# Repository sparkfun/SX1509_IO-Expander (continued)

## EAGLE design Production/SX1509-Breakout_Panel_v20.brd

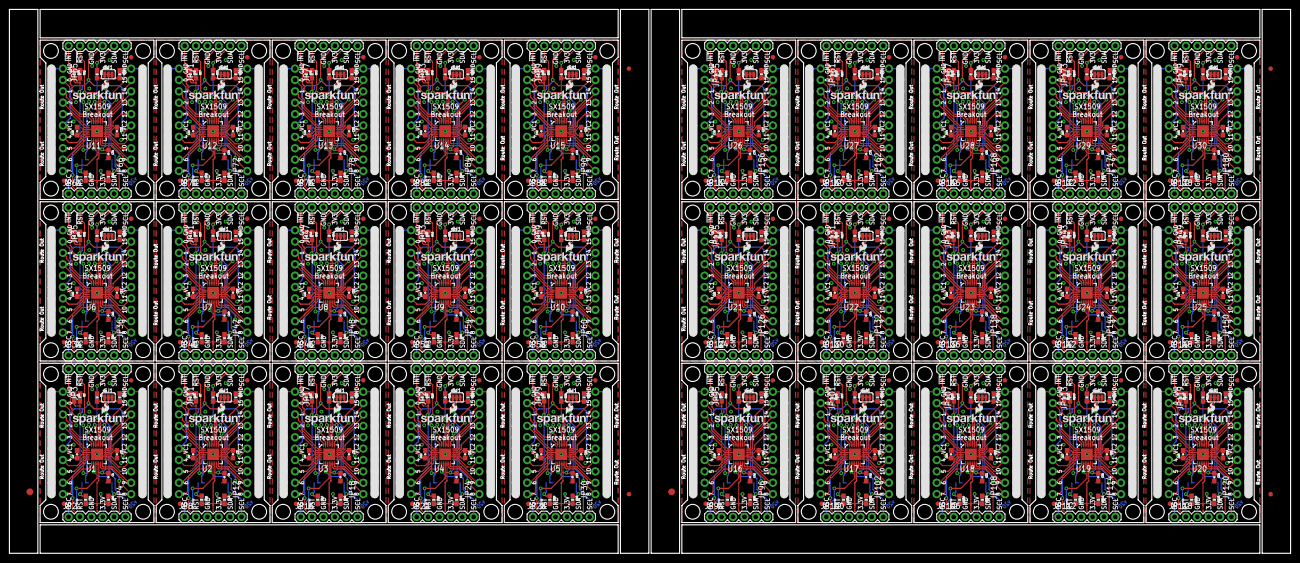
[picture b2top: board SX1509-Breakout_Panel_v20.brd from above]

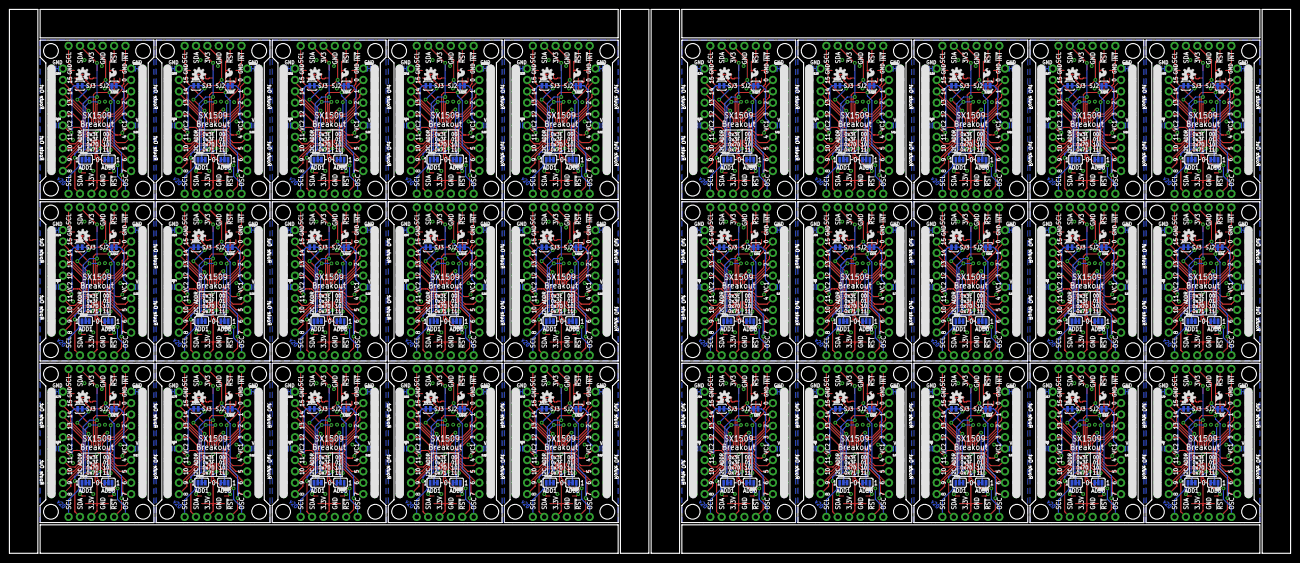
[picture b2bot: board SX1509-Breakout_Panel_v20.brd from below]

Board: 2 copper layers, 286.0 x 121.4 mm, 966 parts (300 on the bottom side), 990 nets.

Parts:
C1, C2, C3, C4, C5, C6, C7, C8, C9, C10, C11, C12, C13, C14, C15, C16, C17, C18, C19, C20, C21, C22, C23, C24, C25, C26, C27, C28, C29, C30, C31, C32, C33, C34, C35, C36, C37, C38, C39, C40, C41, C42, C43, C44, C45, C46, C47, C48, C49, C50, C51, C52, C53, C54, C55, C56, C57, C58, C59, C60, C61, C62, C63, C64, C65, C66, C67, C68, C69, C70, C71, C72, C73, C74, C75, C76, C77, C78, C79, C80, C81, C82, C83, C84, C85, C86, C87, C88, C89, C90: 0.1uF; 0603-CAP
E$1, E$6: FIDUCIAL-1.5X3
E$2, E$3, E$4, E$5: FIDUCIAL-1X2
JP1, JP2, JP7, JP8, JP15, JP16, JP21, JP22, JP27, JP28, JP33, JP34, JP39, JP40, JP45, JP46, JP51, JP52, JP57, JP58, JP63, JP64, JP69, JP70, JP75, JP76, JP81, JP82, JP87, JP88, JP93, JP94, JP99, JP100, JP105, JP106, JP111, JP112, JP117, JP118, JP123, JP124, JP129, JP130, JP135, JP136, JP141, JP142, JP147, JP148, JP153, JP154, JP159, JP160, JP165, JP166, JP171, JP172, JP177, JP178: 1X06
JP3, JP4, JP11, JP12, JP17, JP18, JP23, JP24, JP29, JP30, JP35, JP36, JP41, JP42, JP47, JP48, JP53, JP54, JP59, JP60, JP65, JP66, JP71, JP72, JP77, JP78, JP83, JP84, JP89, JP90, JP95, JP96, JP101, JP102, JP107, JP108, JP113, JP114, JP119, JP120, JP125, JP126, JP131, JP132, JP137, JP138, JP143, JP144, JP149, JP150, JP155, JP156, JP161, JP162, JP167, JP168, JP173, JP174, JP179, JP180: 2X10_ROUND_NOSILK
JP5, JP6, JP9, JP10, JP13, JP14, JP19, JP20, JP25, JP26, JP31, JP32, JP37, JP38, JP43, JP44, JP49, JP50, JP55, JP56, JP61, JP62, JP67, JP68, JP73, JP74, JP79, JP80, JP85, JP86, JP91, JP92, JP97, JP98, JP103, JP104, JP109, JP110, JP115, JP116, JP121, JP122, JP127, JP128, JP133, JP134, JP139, JP140, JP145, JP146, JP151, JP152, JP157, JP158, JP163, JP164, JP169, JP170, JP175, JP176: FIDUCIAL1X2; FIDUCIAL-1X2
LOGO1, LOGO6, LOGO9, LOGO12, LOGO15, LOGO18, LOGO21, LOGO24, LOGO27, LOGO30, LOGO33, LOGO36, LOGO39, LOGO42, LOGO45, LOGO48, LOGO51, LOGO54, LOGO57, LOGO60, LOGO63, LOGO66, LOGO69, LOGO72, LOGO75, LOGO78, LOGO81, LOGO84, LOGO87, LOGO90: SFE_LOGO_NAME_FLAME.1_INCH; SFE_LOGO_NAME_FLAME_.1
LOGO2, LOGO5, LOGO8, LOGO11, LOGO14, LOGO17, LOGO20, LOGO23, LOGO26, LOGO29, LOGO32, LOGO35, LOGO38, LOGO41, LOGO44, LOGO47, LOGO50, LOGO53, LOGO56, LOGO59, LOGO62, LOGO65, LOGO68, LOGO71, LOGO74, LOGO77, LOGO80, LOGO83, LOGO86, LOGO89: SFE_LOGO_FLAME.1_INCH; SFE_LOGO_FLAME_.1
LOGO3, LOGO4, LOGO7, LOGO10, LOGO13, LOGO16, LOGO19, LOGO22, LOGO25, LOGO28, LOGO31, LOGO34, LOGO37, LOGO40, LOGO43, LOGO46, LOGO49, LOGO52, LOGO55, LOGO58, LOGO61, LOGO64, LOGO67, LOGO70, LOGO73, LOGO76, LOGO79, LOGO82, LOGO85, LOGO88: OSHW-LOGOS; OSHW-LOGO-S
R1, R2, R3, R4, R5, R6, R7, R8, R9, R10, R11, R12, R13, R14, R15, R16, R17, R18, R19, R20, R21, R22, R23, R24, R25, R26, R27, R28, R29, R30, R31, R32, R33, R34, R35, R36, R37, R38, R39, R40, R41, R42, R43, R44, R45, R46, R47, R48, R49, R50, R51, R52, R53, R54, R55, R56, R57, R58, R59, R60, R61, R62, R63, R64, R65, R66, R67, R68, R69, R70, R71, R72, R73, R74, R75, R76, R77, R78, R79, R80, R81, R82, R83, R84, R85, R86, R87, R88, R89, R90, R91, R92, R93, R94, R95, R96, R97, R98, R99, R100, R101, R102, R103, R104, R105, R106, R107, R108, R109, R110, R111, R112, R113, R114, R115, R116, R117, R118, R119, R120, R121, R122, R123, R124, R125, R126, R127, R128, R129, R130, R131, R132, R133, R134, R135, R136, R137, R138, R139, R140, R141, R142, R143, R144, R145, R146, R147, R148, R149, R150, R151, R152, R153, R154, R155, R156, R157, R158, R159, R160, R161, R162, R163, R164, R165, R166, R167, R168, R169, R170, R171, R172, R173, R174, R175, R176, R177, R178, R179, R180: 10K; 0603-RES
SJ1, SJ14, SJ23, SJ32, SJ41, SJ50, SJ59, SJ68, SJ77, SJ86, SJ95, SJ104, SJ113, SJ122, SJ131, SJ140, SJ149, SJ158, SJ167, SJ176, SJ185, SJ194, SJ203, SJ212, SJ221, SJ230, SJ239, SJ248, SJ257, SJ266: PAD-JUMPER-3-3OF3_NC_BY_TRACE_YES_SILK_FULL_BOX
SJ2, SJ10, SJ19, SJ28, SJ37, SJ46, SJ55, SJ64, SJ73, SJ82, SJ91, SJ100, SJ109, SJ118, SJ127, SJ136, SJ145, SJ154, SJ163, SJ172, SJ181, SJ190, SJ199, SJ208, SJ217, SJ226, SJ235, SJ244, SJ253, SJ262: VCC1-3.3V; PAD-JUMPER-2-NC_BY_TRACE_YES_SILK
SJ3, SJ11, SJ20, SJ29, SJ38, SJ47, SJ56, SJ65, SJ74, SJ83, SJ92, SJ101, SJ110, SJ119, SJ128, SJ137, SJ146, SJ155, SJ164, SJ173, SJ182, SJ191, SJ200, SJ209, SJ218, SJ227, SJ236, SJ245, SJ254, SJ263: VCC2-3.3V; PAD-JUMPER-2-NC_BY_TRACE_YES_SILK
SJ4, SJ5, SJ12, SJ13, SJ21, SJ22, SJ30, SJ31, SJ39, SJ40, SJ48, SJ49, SJ57, SJ58, SJ66, SJ67, SJ75, SJ76, SJ84, SJ85, SJ93, SJ94, SJ102, SJ103, SJ111, SJ112, SJ120, SJ121, SJ129, SJ130, SJ138, SJ139, SJ147, SJ148, SJ156, SJ157, SJ165, SJ166, SJ174, SJ175, SJ183, SJ184, SJ192, SJ193, SJ201, SJ202, SJ210, SJ211, SJ219, SJ220, SJ228, SJ229, SJ237, SJ238, SJ246, SJ247, SJ255, SJ256, SJ264, SJ265: PAD-JUMPER-3-2OF3_NC_BY_TRACE_YES_SILK_FULL_BOX
SJ6, SJ15, SJ24, SJ33, SJ42, SJ51, SJ60, SJ69, SJ78, SJ87, SJ96, SJ105, SJ114, SJ123, SJ132, SJ141, SJ150, SJ159, SJ168, SJ177, SJ186, SJ195, SJ204, SJ213, SJ222, SJ231, SJ240, SJ249, SJ258, SJ267: A-VCC1; PAD-JUMPER-2-NO_NO_SILK
SJ7, SJ9, SJ17, SJ18, SJ26, SJ27, SJ35, SJ36, SJ44, SJ45, SJ53, SJ54, SJ62, SJ63, SJ71, SJ72, SJ80, SJ81, SJ89, SJ90, SJ98, SJ99, SJ107, SJ108, SJ116, SJ117, SJ125, SJ126, SJ134, SJ135, SJ143, SJ144, SJ152, SJ153, SJ161, SJ162, SJ170, SJ171, SJ179, SJ180, SJ188, SJ189, SJ197, SJ198, SJ206, SJ207, SJ215, SJ216, SJ224, SJ225, SJ233, SJ234, SJ242, SJ243, SJ251, SJ252, SJ260, SJ261, SJ269, SJ270: GND; PAD-JUMPER-2-NC_BY_TRACE_NO_SILK
SJ8, SJ16, SJ25, SJ34, SJ43, SJ52, SJ61, SJ70, SJ79, SJ88, SJ97, SJ106, SJ115, SJ124, SJ133, SJ142, SJ151, SJ160, SJ169, SJ178, SJ187, SJ196, SJ205, SJ214, SJ223, SJ232, SJ241, SJ250, SJ259, SJ268: B-VCC2; PAD-JUMPER-2-NO_NO_SILK
STANDOFF1, STANDOFF2, STANDOFF3, STANDOFF4, STANDOFF5, STANDOFF6, STANDOFF7, STANDOFF8, STANDOFF9, STANDOFF10, STANDOFF11, STANDOFF12, STANDOFF13, STANDOFF14, STANDOFF15, STANDOFF16, STANDOFF17, STANDOFF18, STANDOFF19, STANDOFF20, STANDOFF21, STANDOFF22, STANDOFF23, STANDOFF24, STANDOFF25, STANDOFF26, STANDOFF27, STANDOFF28, STANDOFF29, STANDOFF30, STANDOFF31, STANDOFF32, STANDOFF33, STANDOFF34, STANDOFF35, STANDOFF36, STANDOFF37, STANDOFF38, STANDOFF39, STANDOFF40, STANDOFF41, STANDOFF42, STANDOFF43, STANDOFF44, STANDOFF45, STANDOFF46, STANDOFF47, STANDOFF48, STANDOFF49, STANDOFF50, STANDOFF51, STANDOFF52, STANDOFF53, STANDOFF54, STANDOFF55, STANDOFF56, STANDOFF57, STANDOFF58, STANDOFF59, STANDOFF60, STANDOFF61, STANDOFF62, STANDOFF63, STANDOFF64, STANDOFF65, STANDOFF66, STANDOFF67, STANDOFF68, STANDOFF69, STANDOFF70, STANDOFF71, STANDOFF72, STANDOFF73, STANDOFF74, STANDOFF75, STANDOFF76, STANDOFF77, STANDOFF78, STANDOFF79, STANDOFF80, STANDOFF81, STANDOFF82, STANDOFF83, STANDOFF84, STANDOFF85, STANDOFF86, STANDOFF87, STANDOFF88, STANDOFF89, STANDOFF90, STANDOFF91, STANDOFF92, STANDOFF93, STANDOFF94, STANDOFF95, STANDOFF96, STANDOFF97, STANDOFF98, STANDOFF99, STANDOFF100, STANDOFF101, STANDOFF102, STANDOFF103, STANDOFF104, STANDOFF105, STANDOFF106, STANDOFF107, STANDOFF108, STANDOFF109, STANDOFF110, STANDOFF111, STANDOFF112, STANDOFF113, STANDOFF114, STANDOFF115, STANDOFF116, STANDOFF117, STANDOFF118, STANDOFF119, STANDOFF120: STAND-OFF
U1, U2, U3, U4, U5, U6, U7, U8, U9, U10, U11, U12, U13, U14, U15, U16, U17, U18, U19, U20, U21, U22, U23, U24, U25, U26, U27, U28, U29, U30: SX1509; QFN-28

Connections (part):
0: JP3.4, U1.27
1: JP3.6, U1.28
2: JP3.8, U1.1
3: JP3.10, U1.2
3.3V: C1.1, JP1.4, JP2.4, R1.2, R3.2, R5.2, R6.2, SJ1.2, SJ2.2, SJ3.2, U1.12
3.3V1: C4.1, JP7.4, JP8.4, R7.2, R10.2, R11.2, R12.2, SJ10.2, SJ11.2, SJ14.2, U2.12
3.3V2: C7.1, JP15.4, JP16.4, R13.2, R16.2, R17.2, R18.2, SJ19.2, SJ20.2, SJ23.2, U3.12
3.3V3: C10.1, JP21.4, JP22.4, R19.2, R22.2, R23.2, R24.2, SJ28.2, SJ29.2, SJ32.2, U4.12
3.3V4: C13.1, JP27.4, JP28.4, R25.2, R28.2, R29.2, R30.2, SJ37.2, SJ38.2, SJ41.2, U5.12
3.3V5: C16.1, JP33.4, JP34.4, R31.2, R34.2, R35.2, R36.2, SJ46.2, SJ47.2, SJ50.2, U6.12
3.3V6: C19.1, JP39.4, JP40.4, R37.2, R40.2, R41.2, R42.2, SJ55.2, SJ56.2, SJ59.2, U7.12
3.3V7: C22.1, JP45.4, JP46.4, R43.2, R46.2, R47.2, R48.2, SJ64.2, SJ65.2, SJ68.2, U8.12
3.3V8: C25.1, JP51.4, JP52.4, R49.2, R52.2, R53.2, R54.2, SJ73.2, SJ74.2, SJ77.2, U9.12
3.3V9: C28.1, JP57.4, JP58.4, R55.2, R58.2, R59.2, R60.2, SJ82.2, SJ83.2, SJ86.2, U10.12
3.3V10: C31.1, JP63.4, JP64.4, R61.2, R64.2, R65.2, R66.2, SJ91.2, SJ92.2, SJ95.2, U11.12
3.3V11: C34.1, JP69.4, JP70.4, R67.2, R70.2, R71.2, R72.2, SJ100.2, SJ101.2, SJ104.2, U12.12
3.3V12: C37.1, JP75.4, JP76.4, R73.2, R76.2, R77.2, R78.2, SJ109.2, SJ110.2, SJ113.2, U13.12
3.3V13: C40.1, JP81.4, JP82.4, R79.2, R82.2, R83.2, R84.2, SJ118.2, SJ119.2, SJ122.2, U14.12
3.3V14: C43.1, JP87.4, JP88.4, R85.2, R88.2, R89.2, R90.2, SJ127.2, SJ128.2, SJ131.2, U15.12
3.3V15: C46.1, JP93.4, JP94.4, R91.2, R94.2, R95.2, R96.2, SJ136.2, SJ137.2, SJ140.2, U16.12
3.3V16: C49.1, JP99.4, JP100.4, R97.2, R100.2, R101.2, R102.2, SJ145.2, SJ146.2, SJ149.2, U17.12
3.3V17: C52.1, JP105.4, JP106.4, R103.2, R106.2, R107.2, R108.2, SJ154.2, SJ155.2, SJ158.2, U18.12
3.3V18: C55.1, JP111.4, JP112.4, R109.2, R112.2, R113.2, R114.2, SJ163.2, SJ164.2, SJ167.2, U19.12
3.3V19: C58.1, JP117.4, JP118.4, R115.2, R118.2, R119.2, R120.2, SJ172.2, SJ173.2, SJ176.2, U20.12
3.3V20: C61.1, JP123.4, JP124.4, R121.2, R124.2, R125.2, R126.2, SJ181.2, SJ182.2, SJ185.2, U21.12
3.3V21: C64.1, JP129.4, JP130.4, R127.2, R130.2, R131.2, R132.2, SJ190.2, SJ191.2, SJ194.2, U22.12
3.3V22: C67.1, JP135.4, JP136.4, R133.2, R136.2, R137.2, R138.2, SJ199.2, SJ200.2, SJ203.2, U23.12
3.3V23: C70.1, JP141.4, JP142.4, R139.2, R142.2, R143.2, R144.2, SJ208.2, SJ209.2, SJ212.2, U24.12
3.3V24: C73.1, JP147.4, JP148.4, R145.2, R148.2, R149.2, R150.2, SJ217.2, SJ218.2, SJ221.2, U25.12
3.3V25: C76.1, JP153.4, JP154.4, R151.2, R154.2, R155.2, R156.2, SJ226.2, SJ227.2, SJ230.2, U26.12
3.3V26: C79.1, JP159.4, JP160.4, R157.2, R160.2, R161.2, R162.2, SJ235.2, SJ236.2, SJ239.2, U27.12
3.3V27: C82.1, JP165.4, JP166.4, R163.2, R166.2, R167.2, R168.2, SJ244.2, SJ245.2, SJ248.2, U28.12
3.3V28: C85.1, JP171.4, JP172.4, R169.2, R172.2, R173.2, R174.2, SJ253.2, SJ254.2, SJ257.2, U29.12
3.3V29: C88.1, JP177.4, JP178.4, R175.2, R178.2, R179.2, R180.2, SJ262.2, SJ263.2, SJ266.2, U30.12
4: JP3.14, U1.5
5: JP3.16, U1.6
6: JP3.18, U1.7
7: JP3.20, U1.8
8: JP4.2, U1.13
9: JP4.4, U1.14
10: JP4.6, U1.15
11: JP4.8, U1.16
12: JP4.12, U1.19
13: JP4.14, U1.20
14: JP4.16, U1.21
15: JP4.18, U1.22
16: JP12.2, U2.13
17: JP12.4, U2.14
18: JP12.6, U2.15
19: JP12.8, U2.16
20: JP12.12, U2.19
21: JP12.14, U2.20
22: JP12.16, U2.21
23: JP12.18, U2.22
24: JP11.4, U2.27
25: JP11.6, U2.28
26: JP11.8, U2.1
27: JP11.10, U2.2
28: JP11.14, U2.5
29: JP11.16, U2.6
30: JP11.18, U2.7
31: JP11.20, U2.8
32: JP18.2, U3.13
33: JP18.4, U3.14
34: JP18.6, U3.15
35: JP18.8, U3.16
36: JP18.12, U3.19
37: JP18.14, U3.20
38: JP18.16, U3.21
39: JP18.18, U3.22
40: JP17.4, U3.27
41: JP17.6, U3.28
42: JP17.8, U3.1
43: JP17.10, U3.2
44: JP17.14, U3.5
45: JP17.16, U3.6
46: JP17.18, U3.7
47: JP17.20, U3.8
48: JP24.2, U4.13
49: JP24.4, U4.14
50: JP24.6, U4.15
51: JP24.8, U4.16
52: JP24.12, U4.19
53: JP24.14, U4.20
54: JP24.16, U4.21
55: JP24.18, U4.22
56: JP23.4, U4.27
57: JP23.6, U4.28
58: JP23.8, U4.1
59: JP23.10, U4.2
60: JP23.14, U4.5
61: JP23.16, U4.6
62: JP23.18, U4.7
63: JP23.20, U4.8
64: JP30.2, U5.13
65: JP30.4, U5.14
66: JP30.6, U5.15
67: JP30.8, U5.16
68: JP30.12, U5.19
69: JP30.14, U5.20
70: JP30.16, U5.21
71: JP30.18, U5.22
72: JP29.4, U5.27
73: JP29.6, U5.28
74: JP29.8, U5.1
75: JP29.10, U5.2
76: JP29.14, U5.5
77: JP29.16, U5.6
78: JP29.18, U5.7
79: JP29.20, U5.8
80: JP36.2, U6.13
81: JP36.4, U6.14
82: JP36.6, U6.15
83: JP36.8, U6.16
84: JP36.12, U6.19
85: JP36.14, U6.20
86: JP36.16, U6.21
87: JP36.18, U6.22
88: JP35.4, U6.27
89: JP35.6, U6.28
90: JP35.8, U6.1
91: JP35.10, U6.2
92: JP35.14, U6.5
93: JP35.16, U6.6
94: JP35.18, U6.7
95: JP35.20, U6.8
96: JP42.2, U7.13
97: JP42.4, U7.14
98: JP42.6, U7.15
99: JP42.8, U7.16
100: JP42.12, U7.19
101: JP42.14, U7.20
102: JP42.16, U7.21
103: JP42.18, U7.22
104: JP41.4, U7.27
105: JP41.6, U7.28
106: JP41.8, U7.1
107: JP41.10, U7.2
108: JP41.14, U7.5
109: JP41.16, U7.6
110: JP41.18, U7.7
111: JP41.20, U7.8
112: JP48.2, U8.13
113: JP48.4, U8.14
114: JP48.6, U8.15
115: JP48.8, U8.16
116: JP48.12, U8.19
117: JP48.14, U8.20
118: JP48.16, U8.21
119: JP48.18, U8.22
120: JP47.4, U8.27
121: JP47.6, U8.28
122: JP47.8, U8.1
123: JP47.10, U8.2
124: JP47.14, U8.5
125: JP47.16, U8.6
126: JP47.18, U8.7
127: JP47.20, U8.8
128: JP54.2, U9.13
129: JP54.4, U9.14
130: JP54.6, U9.15
131: JP54.8, U9.16
132: JP54.12, U9.19
133: JP54.14, U9.20
134: JP54.16, U9.21
135: JP54.18, U9.22
136: JP53.4, U9.27
137: JP53.6, U9.28
138: JP53.8, U9.1
139: JP53.10, U9.2
140: JP53.14, U9.5
141: JP53.16, U9.6
142: JP53.18, U9.7
143: JP53.20, U9.8
144: JP60.2, U10.13
145: JP60.4, U10.14
146: JP60.6, U10.15
147: JP60.8, U10.16
148: JP60.12, U10.19
149: JP60.14, U10.20
150: JP60.16, U10.21
151: JP60.18, U10.22
152: JP59.4, U10.27
153: JP59.6, U10.28
154: JP59.8, U10.1
155: JP59.10, U10.2
156: JP59.14, U10.5
157: JP59.16, U10.6
158: JP59.18, U10.7
159: JP59.20, U10.8
160: JP66.2, U11.13
161: JP66.4, U11.14
162: JP66.6, U11.15
163: JP66.8, U11.16
164: JP66.12, U11.19
165: JP66.14, U11.20
166: JP66.16, U11.21
167: JP66.18, U11.22
168: JP65.4, U11.27
169: JP65.6, U11.28
170: JP65.8, U11.1
171: JP65.10, U11.2
172: JP65.14, U11.5
173: JP65.16, U11.6
174: JP65.18, U11.7
175: JP65.20, U11.8
176: JP72.2, U12.13
177: JP72.4, U12.14
178: JP72.6, U12.15
179: JP72.8, U12.16
180: JP72.12, U12.19
181: JP72.14, U12.20
182: JP72.16, U12.21
183: JP72.18, U12.22
184: JP71.4, U12.27
185: JP71.6, U12.28
186: JP71.8, U12.1
187: JP71.10, U12.2
188: JP71.14, U12.5
189: JP71.16, U12.6
190: JP71.18, U12.7
191: JP71.20, U12.8
192: JP78.2, U13.13
193: JP78.4, U13.14
194: JP78.6, U13.15
195: JP78.8, U13.16
196: JP78.12, U13.19
197: JP78.14, U13.20
198: JP78.16, U13.21
199: JP78.18, U13.22
200: JP77.4, U13.27
201: JP77.6, U13.28
202: JP77.8, U13.1
203: JP77.10, U13.2
204: JP77.14, U13.5
205: JP77.16, U13.6
206: JP77.18, U13.7
207: JP77.20, U13.8
208: JP84.2, U14.13
209: JP84.4, U14.14
210: JP84.6, U14.15
211: JP84.8, U14.16
212: JP84.12, U14.19
213: JP84.14, U14.20
214: JP84.16, U14.21
215: JP84.18, U14.22
216: JP83.4, U14.27
217: JP83.6, U14.28
218: JP83.8, U14.1
219: JP83.10, U14.2
220: JP83.14, U14.5
221: JP83.16, U14.6
222: JP83.18, U14.7
223: JP83.20, U14.8
224: JP90.2, U15.13
225: JP90.4, U15.14
226: JP90.6, U15.15
227: JP90.8, U15.16
228: JP90.12, U15.19
229: JP90.14, U15.20
230: JP90.16, U15.21
231: JP90.18, U15.22
232: JP89.4, U15.27
233: JP89.6, U15.28
234: JP89.8, U15.1
235: JP89.10, U15.2
236: JP89.14, U15.5
237: JP89.16, U15.6
238: JP89.18, U15.7
239: JP89.20, U15.8
240: JP96.2, U16.13
241: JP96.4, U16.14
242: JP96.6, U16.15
243: JP96.8, U16.16
244: JP96.12, U16.19
245: JP96.14, U16.20
246: JP96.16, U16.21
247: JP96.18, U16.22
248: JP95.4, U16.27
249: JP95.6, U16.28
250: JP95.8, U16.1
251: JP95.10, U16.2
252: JP95.14, U16.5
253: JP95.16, U16.6
254: JP95.18, U16.7
255: JP95.20, U16.8
256: JP102.2, U17.13
257: JP102.4, U17.14
258: JP102.6, U17.15
259: JP102.8, U17.16
260: JP102.12, U17.19
261: JP102.14, U17.20
262: JP102.16, U17.21
263: JP102.18, U17.22
264: JP101.4, U17.27
265: JP101.6, U17.28
266: JP101.8, U17.1
267: JP101.10, U17.2
268: JP101.14, U17.5
269: JP101.16, U17.6
270: JP101.18, U17.7
271: JP101.20, U17.8
272: JP108.2, U18.13
273: JP108.4, U18.14
274: JP108.6, U18.15
275: JP108.8, U18.16
276: JP108.12, U18.19
277: JP108.14, U18.20
278: JP108.16, U18.21
279: JP108.18, U18.22
280: JP107.4, U18.27
281: JP107.6, U18.28
282: JP107.8, U18.1
283: JP107.10, U18.2
284: JP107.14, U18.5
285: JP107.16, U18.6
286: JP107.18, U18.7
287: JP107.20, U18.8
288: JP114.2, U19.13
289: JP114.4, U19.14
290: JP114.6, U19.15
291: JP114.8, U19.16
292: JP114.12, U19.19
293: JP114.14, U19.20
294: JP114.16, U19.21
295: JP114.18, U19.22
296: JP113.4, U19.27
297: JP113.6, U19.28
298: JP113.8, U19.1
299: JP113.10, U19.2
300: JP113.14, U19.5
301: JP113.16, U19.6
302: JP113.18, U19.7
303: JP113.20, U19.8
304: JP120.2, U20.13
305: JP120.4, U20.14
306: JP120.6, U20.15
307: JP120.8, U20.16
308: JP120.12, U20.19
309: JP120.14, U20.20
310: JP120.16, U20.21
311: JP120.18, U20.22
312: JP119.4, U20.27
313: JP119.6, U20.28
314: JP119.8, U20.1
315: JP119.10, U20.2
316: JP119.14, U20.5
317: JP119.16, U20.6
318: JP119.18, U20.7
319: JP119.20, U20.8
320: JP126.2, U21.13
321: JP126.4, U21.14
322: JP126.6, U21.15
323: JP126.8, U21.16
324: JP126.12, U21.19
325: JP126.14, U21.20
326: JP126.16, U21.21
327: JP126.18, U21.22
328: JP125.4, U21.27
329: JP125.6, U21.28
330: JP125.8, U21.1
331: JP125.10, U21.2
332: JP125.14, U21.5
333: JP125.16, U21.6
334: JP125.18, U21.7
335: JP125.20, U21.8
336: JP132.2, U22.13
337: JP132.4, U22.14
338: JP132.6, U22.15
339: JP132.8, U22.16
340: JP132.12, U22.19
341: JP132.14, U22.20
342: JP132.16, U22.21
343: JP132.18, U22.22
344: JP131.4, U22.27
345: JP131.6, U22.28
346: JP131.8, U22.1
347: JP131.10, U22.2
348: JP131.14, U22.5
349: JP131.16, U22.6
350: JP131.18, U22.7
351: JP131.20, U22.8
352: JP138.2, U23.13
353: JP138.4, U23.14
354: JP138.6, U23.15
355: JP138.8, U23.16
356: JP138.12, U23.19
357: JP138.14, U23.20
358: JP138.16, U23.21
359: JP138.18, U23.22
360: JP137.4, U23.27
361: JP137.6, U23.28
362: JP137.8, U23.1
363: JP137.10, U23.2
364: JP137.14, U23.5
365: JP137.16, U23.6
366: JP137.18, U23.7
367: JP137.20, U23.8
368: JP144.2, U24.13
369: JP144.4, U24.14
370: JP144.6, U24.15
371: JP144.8, U24.16
372: JP144.12, U24.19
373: JP144.14, U24.20
374: JP144.16, U24.21
375: JP144.18, U24.22
376: JP143.4, U24.27
377: JP143.6, U24.28
378: JP143.8, U24.1
379: JP143.10, U24.2
380: JP143.14, U24.5
381: JP143.16, U24.6
382: JP143.18, U24.7
383: JP143.20, U24.8
384: JP150.2, U25.13
385: JP150.4, U25.14
386: JP150.6, U25.15
387: JP150.8, U25.16
388: JP150.12, U25.19
389: JP150.14, U25.20
390: JP150.16, U25.21
391: JP150.18, U25.22
392: JP149.4, U25.27
393: JP149.6, U25.28
394: JP149.8, U25.1
395: JP149.10, U25.2
396: JP149.14, U25.5
397: JP149.16, U25.6
398: JP149.18, U25.7
399: JP149.20, U25.8
400: JP156.2, U26.13
401: JP156.4, U26.14
402: JP156.6, U26.15
403: JP156.8, U26.16
404: JP156.12, U26.19
405: JP156.14, U26.20
406: JP156.16, U26.21
407: JP156.18, U26.22
408: JP155.4, U26.27
409: JP155.6, U26.28
410: JP155.8, U26.1
411: JP155.10, U26.2
412: JP155.14, U26.5
413: JP155.16, U26.6
414: JP155.18, U26.7
415: JP155.20, U26.8
416: JP162.2, U27.13
417: JP162.4, U27.14
418: JP162.6, U27.15
419: JP162.8, U27.16
420: JP162.12, U27.19
421: JP162.14, U27.20
422: JP162.16, U27.21
423: JP162.18, U27.22
424: JP161.4, U27.27
425: JP161.6, U27.28
426: JP161.8, U27.1
427: JP161.10, U27.2
428: JP161.14, U27.5
429: JP161.16, U27.6
430: JP161.18, U27.7
431: JP161.20, U27.8
432: JP168.2, U28.13
433: JP168.4, U28.14
434: JP168.6, U28.15
435: JP168.8, U28.16
436: JP168.12, U28.19
437: JP168.14, U28.20
438: JP168.16, U28.21
439: JP168.18, U28.22
440: JP167.4, U28.27
441: JP167.6, U28.28
442: JP167.8, U28.1
443: JP167.10, U28.2
444: JP167.14, U28.5
445: JP167.16, U28.6
446: JP167.18, U28.7
447: JP167.20, U28.8
448: JP174.2, U29.13
449: JP174.4, U29.14
450: JP174.6, U29.15
451: JP174.8, U29.16
452: JP174.12, U29.19
453: JP174.14, U29.20
454: JP174.16, U29.21
455: JP174.18, U29.22
456: JP173.4, U29.27
457: JP173.6, U29.28
458: JP173.8, U29.1
459: JP173.10, U29.2
460: JP173.14, U29.5
461: JP173.16, U29.6
462: JP173.18, U29.7
463: JP173.20, U29.8
464: JP180.2, U30.13
465: JP180.4, U30.14
466: JP180.6, U30.15
467: JP180.8, U30.16
468: JP180.12, U30.19
469: JP180.14, U30.20
470: JP180.16, U30.21
471: JP180.18, U30.22
472: JP179.4, U30.27
473: JP179.6, U30.28
474: JP179.8, U30.1
475: JP179.10, U30.2
476: JP179.14, U30.5
477: JP179.16, U30.6
478: JP179.18, U30.7
479: JP179.20, U30.8
!INT: JP1.1, R1.1, U1.9
!INT1: JP7.1, R10.1, U2.9
!INT2: JP15.1, R16.1, U3.9
!INT3: JP21.1, R22.1, U4.9
!INT4: JP27.1, R28.1, U5.9
!INT5: JP33.1, R34.1, U6.9
!INT6: JP39.1, R40.1, U7.9
!INT7: JP45.1, R46.1, U8.9
!INT8: JP51.1, R52.1, U9.9
!INT9: JP57.1, R58.1, U10.9
!INT10: JP63.1, R64.1, U11.9
!INT11: JP69.1, R70.1, U12.9
!INT12: JP75.1, R76.1, U13.9
!INT13: JP81.1, R82.1, U14.9
!INT14: JP87.1, R88.1, U15.9
!INT15: JP93.1, R94.1, U16.9
!INT16: JP99.1, R100.1, U17.9
!INT17: JP105.1, R106.1, U18.9
!INT18: JP111.1, R112.1, U19.9
!INT19: JP117.1, R118.1, U20.9
!INT20: JP123.1, R124.1, U21.9
!INT21: JP129.1, R130.1, U22.9
!INT22: JP135.1, R136.1, U23.9
!INT23: JP141.1, R142.1, U24.9
!INT24: JP147.1, R148.1, U25.9
!INT25: JP153.1, R154.1, U26.9
!INT26: JP159.1, R160.1, U27.9
!INT27: JP165.1, R166.1, U28.9
!INT28: JP171.1, R172.1, U29.9
!INT29: JP177.1, R178.1, U30.9
!RESET: JP1.2, JP2.2, R3.1, U1.23
!RESET1: JP7.2, JP8.2, R7.1, U2.23
!RESET2: JP15.2, JP16.2, R13.1, U3.23
!RESET3: JP21.2, JP22.2, R19.1, U4.23
!RESET4: JP27.2, JP28.2, R25.1, U5.23
!RESET5: JP33.2, JP34.2, R31.1, U6.23
!RESET6: JP39.2, JP40.2, R37.1, U7.23
!RESET7: JP45.2, JP46.2, R43.1, U8.23
!RESET8: JP51.2, JP52.2, R49.1, U9.23
!RESET9: JP57.2, JP58.2, R55.1, U10.23
!RESET10: JP63.2, JP64.2, R61.1, U11.23
!RESET11: JP69.2, JP70.2, R67.1, U12.23
!RESET12: JP75.2, JP76.2, R73.1, U13.23
!RESET13: JP81.2, JP82.2, R79.1, U14.23
!RESET14: JP87.2, JP88.2, R85.1, U15.23
!RESET15: JP93.2, JP94.2, R91.1, U16.23
!RESET16: JP99.2, JP100.2, R97.1, U17.23
!RESET17: JP105.2, JP106.2, R103.1, U18.23
!RESET18: JP111.2, JP112.2, R109.1, U19.23
!RESET19: JP117.2, JP118.2, R115.1, U20.23
!RESET20: JP123.2, JP124.2, R121.1, U21.23
!RESET21: JP129.2, JP130.2, R127.1, U22.23
!RESET22: JP135.2, JP136.2, R133.1, U23.23
!RESET23: JP141.2, JP142.2, R139.1, U24.23
!RESET24: JP147.2, JP148.2, R145.1, U25.23
!RESET25: JP153.2, JP154.2, R151.1, U26.23
!RESET26: JP159.2, JP160.2, R157.1, U27.23
!RESET27: JP165.2, JP166.2, R163.1, U28.23
!RESET28: JP171.2, JP172.2, R169.1, U29.23
!RESET29: JP177.2, JP178.2, R175.1, U30.23
ADDR0: SJ4.2, U1.26
ADDR1: SJ5.2, U1.10
ADDR2: SJ13.2, U2.26
ADDR3: SJ12.2, U2.10
ADDR4: SJ22.2, U3.26
ADDR5: SJ21.2, U3.10
ADDR6: SJ31.2, U4.26
ADDR7: SJ30.2, U4.10
ADDR8: SJ40.2, U5.26
ADDR9: SJ39.2, U5.10
ADDR10: SJ49.2, U6.26
ADDR11: SJ48.2, U6.10
ADDR12: SJ58.2, U7.26
ADDR13: SJ57.2, U7.10
ADDR14: SJ67.2, U8.26
ADDR15: SJ66.2, U8.10
ADDR16: SJ76.2, U9.26
ADDR17: SJ75.2, U9.10
ADDR18: SJ85.2, U10.26
ADDR19: SJ84.2, U10.10
ADDR20: SJ94.2, U11.26
ADDR21: SJ93.2, U11.10
ADDR22: SJ103.2, U12.26
ADDR23: SJ102.2, U12.10
ADDR24: SJ112.2, U13.26
ADDR25: SJ111.2, U13.10
ADDR26: SJ121.2, U14.26
ADDR27: SJ120.2, U14.10
ADDR28: SJ130.2, U15.26
ADDR29: SJ129.2, U15.10
ADDR30: SJ139.2, U16.26
ADDR31: SJ138.2, U16.10
ADDR32: SJ148.2, U17.26
ADDR33: SJ147.2, U17.10
ADDR34: SJ157.2, U18.26
ADDR35: SJ156.2, U18.10
ADDR36: SJ166.2, U19.26
ADDR37: SJ165.2, U19.10
ADDR38: SJ175.2, U20.26
ADDR39: SJ174.2, U20.10
ADDR40: SJ184.2, U21.26
ADDR41: SJ183.2, U21.10
ADDR42: SJ193.2, U22.26
ADDR43: SJ192.2, U22.10
ADDR44: SJ202.2, U23.26
ADDR45: SJ201.2, U23.10
ADDR46: SJ211.2, U24.26
ADDR47: SJ210.2, U24.10
ADDR48: SJ220.2, U25.26
ADDR49: SJ219.2, U25.10
ADDR50: SJ229.2, U26.26
ADDR51: SJ228.2, U26.10
ADDR52: SJ238.2, U27.26
ADDR53: SJ237.2, U27.10
ADDR54: SJ247.2, U28.26
ADDR55: SJ246.2, U28.10
ADDR56: SJ256.2, U29.26
ADDR57: SJ255.2, U29.10
ADDR58: SJ265.2, U30.26
ADDR59: SJ264.2, U30.10
GND: C1.2, C2.2, C3.2, JP1.3, JP2.3, JP3.2, JP4.20, SJ4.3, SJ5.3, SJ7.1, SJ9.1, U1.3, U1.17, U1.29
GND1: C4.2, C5.2, C6.2, JP7.3, JP8.3, JP11.2, JP12.20, SJ12.3, SJ13.3, SJ17.1, SJ18.1, U2.3, U2.17, U2.29
GND2: C7.2, C8.2, C9.2, JP15.3, JP16.3, JP17.2, JP18.20, SJ21.3, SJ22.3, SJ26.1, SJ27.1, U3.3, U3.17, U3.29
GND3: C10.2, C11.2, C12.2, JP21.3, JP22.3, JP23.2, JP24.20, SJ30.3, SJ31.3, SJ35.1, SJ36.1, U4.3, U4.17, U4.29
GND4: C13.2, C14.2, C15.2, JP27.3, JP28.3, JP29.2, JP30.20, SJ39.3, SJ40.3, SJ44.1, SJ45.1, U5.3, U5.17, U5.29
GND5: C16.2, C17.2, C18.2, JP33.3, JP34.3, JP35.2, JP36.20, SJ48.3, SJ49.3, SJ53.1, SJ54.1, U6.3, U6.17, U6.29
GND6: C19.2, C20.2, C21.2, JP39.3, JP40.3, JP41.2, JP42.20, SJ57.3, SJ58.3, SJ62.1, SJ63.1, U7.3, U7.17, U7.29
GND7: C22.2, C23.2, C24.2, JP45.3, JP46.3, JP47.2, JP48.20, SJ66.3, SJ67.3, SJ71.1, SJ72.1, U8.3, U8.17, U8.29
GND8: C25.2, C26.2, C27.2, JP51.3, JP52.3, JP53.2, JP54.20, SJ75.3, SJ76.3, SJ80.1, SJ81.1, U9.3, U9.17, U9.29
GND9: C28.2, C29.2, C30.2, JP57.3, JP58.3, JP59.2, JP60.20, SJ84.3, SJ85.3, SJ89.1, SJ90.1, U10.3, U10.17, U10.29
GND10: C31.2, C32.2, C33.2, JP63.3, JP64.3, JP65.2, JP66.20, SJ93.3, SJ94.3, SJ98.1, SJ99.1, U11.3, U11.17, U11.29
GND11: C34.2, C35.2, C36.2, JP69.3, JP70.3, JP71.2, JP72.20, SJ102.3, SJ103.3, SJ107.1, SJ108.1, U12.3, U12.17, U12.29
GND12: C37.2, C38.2, C39.2, JP75.3, JP76.3, JP77.2, JP78.20, SJ111.3, SJ112.3, SJ116.1, SJ117.1, U13.3, U13.17, U13.29
GND13: C40.2, C41.2, C42.2, JP81.3, JP82.3, JP83.2, JP84.20, SJ120.3, SJ121.3, SJ125.1, SJ126.1, U14.3, U14.17, U14.29
GND14: C43.2, C44.2, C45.2, JP87.3, JP88.3, JP89.2, JP90.20, SJ129.3, SJ130.3, SJ134.1, SJ135.1, U15.3, U15.17, U15.29
GND15: C46.2, C47.2, C48.2, JP93.3, JP94.3, JP95.2, JP96.20, SJ138.3, SJ139.3, SJ143.1, SJ144.1, U16.3, U16.17, U16.29
GND16: C49.2, C50.2, C51.2, JP99.3, JP100.3, JP101.2, JP102.20, SJ147.3, SJ148.3, SJ152.1, SJ153.1, U17.3, U17.17, U17.29
GND17: C52.2, C53.2, C54.2, JP105.3, JP106.3, JP107.2, JP108.20, SJ156.3, SJ157.3, SJ161.1, SJ162.1, U18.3, U18.17, U18.29
GND18: C55.2, C56.2, C57.2, JP111.3, JP112.3, JP113.2, JP114.20, SJ165.3, SJ166.3, SJ170.1, SJ171.1, U19.3, U19.17, U19.29
GND19: C58.2, C59.2, C60.2, JP117.3, JP118.3, JP119.2, JP120.20, SJ174.3, SJ175.3, SJ179.1, SJ180.1, U20.3, U20.17, U20.29
GND20: C61.2, C62.2, C63.2, JP123.3, JP124.3, JP125.2, JP126.20, SJ183.3, SJ184.3, SJ188.1, SJ189.1, U21.3, U21.17, U21.29
GND21: C64.2, C65.2, C66.2, JP129.3, JP130.3, JP131.2, JP132.20, SJ192.3, SJ193.3, SJ197.1, SJ198.1, U22.3, U22.17, U22.29
GND22: C67.2, C68.2, C69.2, JP135.3, JP136.3, JP137.2, JP138.20, SJ201.3, SJ202.3, SJ206.1, SJ207.1, U23.3, U23.17, U23.29
GND23: C70.2, C71.2, C72.2, JP141.3, JP142.3, JP143.2, JP144.20, SJ210.3, SJ211.3, SJ215.1, SJ216.1, U24.3, U24.17, U24.29
GND24: C73.2, C74.2, C75.2, JP147.3, JP148.3, JP149.2, JP150.20, SJ219.3, SJ220.3, SJ224.1, SJ225.1, U25.3, U25.17, U25.29
GND25: C76.2, C77.2, C78.2, JP153.3, JP154.3, JP155.2, JP156.20, SJ228.3, SJ229.3, SJ233.1, SJ234.1, U26.3, U26.17, U26.29
GND26: C79.2, C80.2, C81.2, JP159.3, JP160.3, JP161.2, JP162.20, SJ237.3, SJ238.3, SJ242.1, SJ243.1, U27.3, U27.17, U27.29
GND27: C82.2, C83.2, C84.2, JP165.3, JP166.3, JP167.2, JP168.20, SJ246.3, SJ247.3, SJ251.1, SJ252.1, U28.3, U28.17, U28.29
GND28: C85.2, C86.2, C87.2, JP171.3, JP172.3, JP173.2, JP174.20, SJ255.3, SJ256.3, SJ260.1, SJ261.1, U29.3, U29.17, U29.29
GND29: C88.2, C89.2, C90.2, JP177.3, JP178.3, JP179.2, JP180.20, SJ264.3, SJ265.3, SJ269.1, SJ270.1, U30.3, U30.17, U30.29
unnamed: R2.2, SJ1.3
unnamed: R4.2, SJ1.1
unnamed: JP4.1, JP4.3, JP4.5, JP4.7, JP4.9, JP4.11, JP4.13, JP4.15, JP4.17, JP4.19, SJ8.1, SJ9.2
unnamed: R9.2, SJ14.3
unnamed: R8.2, SJ14.1
unnamed: R11.1, SJ13.1
unnamed: R12.1, SJ12.1
unnamed: R5.1, SJ4.1
unnamed: R6.1, SJ5.1
unnamed: JP12.1, JP12.3, JP12.5, JP12.7, JP12.9, JP12.11, JP12.13, JP12.15, JP12.17, JP12.19, SJ16.1, SJ17.2
unnamed: R15.2, SJ23.3
unnamed: R14.2, SJ23.1
unnamed: R17.1, SJ22.1
unnamed: R18.1, SJ21.1
unnamed: JP18.1, JP18.3, JP18.5, JP18.7, JP18.9, JP18.11, JP18.13, JP18.15, JP18.17, JP18.19, SJ25.1, SJ26.2
unnamed: R21.2, SJ32.3
unnamed: R20.2, SJ32.1
unnamed: R23.1, SJ31.1
unnamed: R24.1, SJ30.1
unnamed: JP24.1, JP24.3, JP24.5, JP24.7, JP24.9, JP24.11, JP24.13, JP24.15, JP24.17, JP24.19, SJ34.1, SJ35.2
unnamed: R27.2, SJ41.3
unnamed: R26.2, SJ41.1
unnamed: R29.1, SJ40.1
unnamed: R30.1, SJ39.1
unnamed: JP30.1, JP30.3, JP30.5, JP30.7, JP30.9, JP30.11, JP30.13, JP30.15, JP30.17, JP30.19, SJ43.1, SJ44.2
unnamed: R33.2, SJ50.3
unnamed: R32.2, SJ50.1
unnamed: R35.1, SJ49.1
unnamed: R36.1, SJ48.1
unnamed: JP36.1, JP36.3, JP36.5, JP36.7, JP36.9, JP36.11, JP36.13, JP36.15, JP36.17, JP36.19, SJ52.1, SJ53.2
unnamed: R39.2, SJ59.3
unnamed: R38.2, SJ59.1
unnamed: R41.1, SJ58.1
unnamed: R42.1, SJ57.1
unnamed: JP42.1, JP42.3, JP42.5, JP42.7, JP42.9, JP42.11, JP42.13, JP42.15, JP42.17, JP42.19, SJ61.1, SJ62.2
unnamed: R45.2, SJ68.3
unnamed: R44.2, SJ68.1
unnamed: R47.1, SJ67.1
unnamed: R48.1, SJ66.1
unnamed: JP48.1, JP48.3, JP48.5, JP48.7, JP48.9, JP48.11, JP48.13, JP48.15, JP48.17, JP48.19, SJ70.1, SJ71.2
unnamed: R51.2, SJ77.3
unnamed: R50.2, SJ77.1
unnamed: R53.1, SJ76.1
unnamed: R54.1, SJ75.1
unnamed: JP54.1, JP54.3, JP54.5, JP54.7, JP54.9, JP54.11, JP54.13, JP54.15, JP54.17, JP54.19, SJ79.1, SJ80.2
unnamed: R57.2, SJ86.3
unnamed: R56.2, SJ86.1
unnamed: R59.1, SJ85.1
unnamed: R60.1, SJ84.1
unnamed: JP60.1, JP60.3, JP60.5, JP60.7, JP60.9, JP60.11, JP60.13, JP60.15, JP60.17, JP60.19, SJ88.1, SJ89.2
unnamed: R63.2, SJ95.3
unnamed: R62.2, SJ95.1
unnamed: R65.1, SJ94.1
unnamed: R66.1, SJ93.1
unnamed: JP66.1, JP66.3, JP66.5, JP66.7, JP66.9, JP66.11, JP66.13, JP66.15, JP66.17, JP66.19, SJ97.1, SJ98.2
unnamed: R69.2, SJ104.3
unnamed: R68.2, SJ104.1
unnamed: R71.1, SJ103.1
unnamed: R72.1, SJ102.1
unnamed: JP72.1, JP72.3, JP72.5, JP72.7, JP72.9, JP72.11, JP72.13, JP72.15, JP72.17, JP72.19, SJ106.1, SJ107.2
unnamed: R75.2, SJ113.3
unnamed: R74.2, SJ113.1
unnamed: R77.1, SJ112.1
unnamed: R78.1, SJ111.1
unnamed: JP78.1, JP78.3, JP78.5, JP78.7, JP78.9, JP78.11, JP78.13, JP78.15, JP78.17, JP78.19, SJ115.1, SJ116.2
unnamed: R81.2, SJ122.3
unnamed: R80.2, SJ122.1
unnamed: R83.1, SJ121.1
unnamed: R84.1, SJ120.1
unnamed: JP84.1, JP84.3, JP84.5, JP84.7, JP84.9, JP84.11, JP84.13, JP84.15, JP84.17, JP84.19, SJ124.1, SJ125.2
unnamed: R87.2, SJ131.3
unnamed: R86.2, SJ131.1
unnamed: R89.1, SJ130.1
unnamed: R90.1, SJ129.1
unnamed: JP90.1, JP90.3, JP90.5, JP90.7, JP90.9, JP90.11, JP90.13, JP90.15, JP90.17, JP90.19, SJ133.1, SJ134.2
unnamed: R93.2, SJ140.3
unnamed: R92.2, SJ140.1
unnamed: R95.1, SJ139.1
unnamed: R96.1, SJ138.1
unnamed: JP96.1, JP96.3, JP96.5, JP96.7, JP96.9, JP96.11, JP96.13, JP96.15, JP96.17, JP96.19, SJ142.1, SJ143.2
unnamed: R99.2, SJ149.3
unnamed: R98.2, SJ149.1
unnamed: R101.1, SJ148.1
unnamed: R102.1, SJ147.1
unnamed: JP102.1, JP102.3, JP102.5, JP102.7, JP102.9, JP102.11, JP102.13, JP102.15, JP102.17, JP102.19, SJ151.1, SJ152.2
unnamed: R105.2, SJ158.3
unnamed: R104.2, SJ158.1
unnamed: R107.1, SJ157.1
unnamed: R108.1, SJ156.1
unnamed: JP108.1, JP108.3, JP108.5, JP108.7, JP108.9, JP108.11, JP108.13, JP108.15, JP108.17, JP108.19, SJ160.1, SJ161.2
unnamed: R111.2, SJ167.3
unnamed: R110.2, SJ167.1
unnamed: R113.1, SJ166.1
unnamed: R114.1, SJ165.1
unnamed: JP114.1, JP114.3, JP114.5, JP114.7, JP114.9, JP114.11, JP114.13, JP114.15, JP114.17, JP114.19, SJ169.1, SJ170.2
unnamed: R117.2, SJ176.3
unnamed: R116.2, SJ176.1
unnamed: R119.1, SJ175.1
unnamed: R120.1, SJ174.1
unnamed: JP120.1, JP120.3, JP120.5, JP120.7, JP120.9, JP120.11, JP120.13, JP120.15, JP120.17, JP120.19, SJ178.1, SJ179.2
unnamed: R123.2, SJ185.3
unnamed: R122.2, SJ185.1
unnamed: R125.1, SJ184.1
unnamed: R126.1, SJ183.1
unnamed: JP126.1, JP126.3, JP126.5, JP126.7, JP126.9, JP126.11, JP126.13, JP126.15, JP126.17, JP126.19, SJ187.1, SJ188.2
unnamed: R129.2, SJ194.3
unnamed: R128.2, SJ194.1
unnamed: R131.1, SJ193.1
unnamed: R132.1, SJ192.1
unnamed: JP132.1, JP132.3, JP132.5, JP132.7, JP132.9, JP132.11, JP132.13, JP132.15, JP132.17, JP132.19, SJ196.1, SJ197.2
unnamed: R135.2, SJ203.3
unnamed: R134.2, SJ203.1
unnamed: R137.1, SJ202.1
unnamed: R138.1, SJ201.1
unnamed: JP138.1, JP138.3, JP138.5, JP138.7, JP138.9, JP138.11, JP138.13, JP138.15, JP138.17, JP138.19, SJ205.1, SJ206.2
unnamed: R141.2, SJ212.3
unnamed: R140.2, SJ212.1
unnamed: R143.1, SJ211.1
unnamed: R144.1, SJ210.1
unnamed: JP144.1, JP144.3, JP144.5, JP144.7, JP144.9, JP144.11, JP144.13, JP144.15, JP144.17, JP144.19, SJ214.1, SJ215.2
unnamed: R147.2, SJ221.3
unnamed: R146.2, SJ221.1
unnamed: R149.1, SJ220.1
unnamed: R150.1, SJ219.1
unnamed: JP150.1, JP150.3, JP150.5, JP150.7, JP150.9, JP150.11, JP150.13, JP150.15, JP150.17, JP150.19, SJ223.1, SJ224.2
unnamed: R153.2, SJ230.3
unnamed: R152.2, SJ230.1
unnamed: R155.1, SJ229.1
unnamed: R156.1, SJ228.1
unnamed: JP156.1, JP156.3, JP156.5, JP156.7, JP156.9, JP156.11, JP156.13, JP156.15, JP156.17, JP156.19, SJ232.1, SJ233.2
unnamed: R159.2, SJ239.3
unnamed: R158.2, SJ239.1
unnamed: R161.1, SJ238.1
unnamed: R162.1, SJ237.1
unnamed: JP162.1, JP162.3, JP162.5, JP162.7, JP162.9, JP162.11, JP162.13, JP162.15, JP162.17, JP162.19, SJ241.1, SJ242.2
unnamed: R165.2, SJ248.3
unnamed: R164.2, SJ248.1
unnamed: R167.1, SJ247.1
unnamed: R168.1, SJ246.1
unnamed: JP168.1, JP168.3, JP168.5, JP168.7, JP168.9, JP168.11, JP168.13, JP168.15, JP168.17, JP168.19, SJ250.1, SJ251.2
unnamed: R171.2, SJ257.3
unnamed: R170.2, SJ257.1
unnamed: R173.1, SJ256.1
unnamed: R174.1, SJ255.1
unnamed: JP174.1, JP174.3, JP174.5, JP174.7, JP174.9, JP174.11, JP174.13, JP174.15, JP174.17, JP174.19, SJ259.1, SJ260.2
unnamed: R177.2, SJ266.3
unnamed: R176.2, SJ266.1
unnamed: R179.1, SJ265.1
unnamed: R180.1, SJ264.1
unnamed: JP180.1, JP180.3, JP180.5, JP180.7, JP180.9, JP180.11, JP180.13, JP180.15, JP180.17, JP180.19, SJ268.1, SJ269.2
OSCIO: JP2.1, U1.11
OSCIO1: JP8.1, U2.11
OSCIO2: JP16.1, U3.11
OSCIO3: JP22.1, U4.11
OSCIO4: JP28.1, U5.11
OSCIO5: JP34.1, U6.11
OSCIO6: JP40.1, U7.11
OSCIO7: JP46.1, U8.11
OSCIO8: JP52.1, U9.11
OSCIO9: JP58.1, U10.11
OSCIO10: JP64.1, U11.11
OSCIO11: JP70.1, U12.11
OSCIO12: JP76.1, U13.11
OSCIO13: JP82.1, U14.11
OSCIO14: JP88.1, U15.11
OSCIO15: JP94.1, U16.11
OSCIO16: JP100.1, U17.11
OSCIO17: JP106.1, U18.11
OSCIO18: JP112.1, U19.11
OSCIO19: JP118.1, U20.11
OSCIO20: JP124.1, U21.11
OSCIO21: JP130.1, U22.11
OSCIO22: JP136.1, U23.11
OSCIO23: JP142.1, U24.11
OSCIO24: JP148.1, U25.11
OSCIO25: JP154.1, U26.11
OSCIO26: JP160.1, U27.11
OSCIO27: JP166.1, U28.11
OSCIO28: JP172.1, U29.11
OSCIO29: JP178.1, U30.11
PWRBUSA: JP3.1, JP3.3, JP3.5, JP3.7, JP3.9, JP3.11, JP3.13, JP3.15, JP3.17, JP3.19, SJ6.1, SJ7.2
PWRBUSA1: JP11.1, JP11.3, JP11.5, JP11.7, JP11.9, JP11.11, JP11.13, JP11.15, JP11.17, JP11.19, SJ15.1, SJ18.2
PWRBUSA2: JP17.1, JP17.3, JP17.5, JP17.7, JP17.9, JP17.11, JP17.13, JP17.15, JP17.17, JP17.19, SJ24.1, SJ27.2
PWRBUSA3: JP23.1, JP23.3, JP23.5, JP23.7, JP23.9, JP23.11, JP23.13, JP23.15, JP23.17, JP23.19, SJ33.1, SJ36.2
PWRBUSA4: JP29.1, JP29.3, JP29.5, JP29.7, JP29.9, JP29.11, JP29.13, JP29.15, JP29.17, JP29.19, SJ42.1, SJ45.2
PWRBUSA5: JP35.1, JP35.3, JP35.5, JP35.7, JP35.9, JP35.11, JP35.13, JP35.15, JP35.17, JP35.19, SJ51.1, SJ54.2
PWRBUSA6: JP41.1, JP41.3, JP41.5, JP41.7, JP41.9, JP41.11, JP41.13, JP41.15, JP41.17, JP41.19, SJ60.1, SJ63.2
PWRBUSA7: JP47.1, JP47.3, JP47.5, JP47.7, JP47.9, JP47.11, JP47.13, JP47.15, JP47.17, JP47.19, SJ69.1, SJ72.2
PWRBUSA8: JP53.1, JP53.3, JP53.5, JP53.7, JP53.9, JP53.11, JP53.13, JP53.15, JP53.17, JP53.19, SJ78.1, SJ81.2
PWRBUSA9: JP59.1, JP59.3, JP59.5, JP59.7, JP59.9, JP59.11, JP59.13, JP59.15, JP59.17, JP59.19, SJ87.1, SJ90.2
PWRBUSA10: JP65.1, JP65.3, JP65.5, JP65.7, JP65.9, JP65.11, JP65.13, JP65.15, JP65.17, JP65.19, SJ96.1, SJ99.2
PWRBUSA11: JP71.1, JP71.3, JP71.5, JP71.7, JP71.9, JP71.11, JP71.13, JP71.15, JP71.17, JP71.19, SJ105.1, SJ108.2
PWRBUSA12: JP77.1, JP77.3, JP77.5, JP77.7, JP77.9, JP77.11, JP77.13, JP77.15, JP77.17, JP77.19, SJ114.1, SJ117.2
PWRBUSA13: JP83.1, JP83.3, JP83.5, JP83.7, JP83.9, JP83.11, JP83.13, JP83.15, JP83.17, JP83.19, SJ123.1, SJ126.2
PWRBUSA14: JP89.1, JP89.3, JP89.5, JP89.7, JP89.9, JP89.11, JP89.13, JP89.15, JP89.17, JP89.19, SJ132.1, SJ135.2
PWRBUSA15: JP95.1, JP95.3, JP95.5, JP95.7, JP95.9, JP95.11, JP95.13, JP95.15, JP95.17, JP95.19, SJ141.1, SJ144.2
PWRBUSA16: JP101.1, JP101.3, JP101.5, JP101.7, JP101.9, JP101.11, JP101.13, JP101.15, JP101.17, JP101.19, SJ150.1, SJ153.2
PWRBUSA17: JP107.1, JP107.3, JP107.5, JP107.7, JP107.9, JP107.11, JP107.13, JP107.15, JP107.17, JP107.19, SJ159.1, SJ162.2
PWRBUSA18: JP113.1, JP113.3, JP113.5, JP113.7, JP113.9, JP113.11, JP113.13, JP113.15, JP113.17, JP113.19, SJ168.1, SJ171.2
PWRBUSA19: JP119.1, JP119.3, JP119.5, JP119.7, JP119.9, JP119.11, JP119.13, JP119.15, JP119.17, JP119.19, SJ177.1, SJ180.2
PWRBUSA20: JP125.1, JP125.3, JP125.5, JP125.7, JP125.9, JP125.11, JP125.13, JP125.15, JP125.17, JP125.19, SJ186.1, SJ189.2
PWRBUSA21: JP131.1, JP131.3, JP131.5, JP131.7, JP131.9, JP131.11, JP131.13, JP131.15, JP131.17, JP131.19, SJ195.1, SJ198.2
PWRBUSA22: JP137.1, JP137.3, JP137.5, JP137.7, JP137.9, JP137.11, JP137.13, JP137.15, JP137.17, JP137.19, SJ204.1, SJ207.2
PWRBUSA23: JP143.1, JP143.3, JP143.5, JP143.7, JP143.9, JP143.11, JP143.13, JP143.15, JP143.17, JP143.19, SJ213.1, SJ216.2
PWRBUSA24: JP149.1, JP149.3, JP149.5, JP149.7, JP149.9, JP149.11, JP149.13, JP149.15, JP149.17, JP149.19, SJ222.1, SJ225.2
PWRBUSA25: JP155.1, JP155.3, JP155.5, JP155.7, JP155.9, JP155.11, JP155.13, JP155.15, JP155.17, JP155.19, SJ231.1, SJ234.2
PWRBUSA26: JP161.1, JP161.3, JP161.5, JP161.7, JP161.9, JP161.11, JP161.13, JP161.15, JP161.17, JP161.19, SJ240.1, SJ243.2
PWRBUSA27: JP167.1, JP167.3, JP167.5, JP167.7, JP167.9, JP167.11, JP167.13, JP167.15, JP167.17, JP167.19, SJ249.1, SJ252.2
PWRBUSA28: JP173.1, JP173.3, JP173.5, JP173.7, JP173.9, JP173.11, JP173.13, JP173.15, JP173.17, JP173.19, SJ258.1, SJ261.2
PWRBUSA29: JP179.1, JP179.3, JP179.5, JP179.7, JP179.9, JP179.11, JP179.13, JP179.15, JP179.17, JP179.19, SJ267.1, SJ270.2
SCL: JP1.6, JP2.6, R2.1, U1.25
SCL1: JP7.6, JP8.6, R9.1, U2.25
SCL2: JP15.6, JP16.6, R15.1, U3.25
SCL3: JP21.6, JP22.6, R21.1, U4.25
SCL4: JP27.6, JP28.6, R27.1, U5.25
SCL5: JP33.6, JP34.6, R33.1, U6.25
SCL6: JP39.6, JP40.6, R39.1, U7.25
SCL7: JP45.6, JP46.6, R45.1, U8.25
SCL8: JP51.6, JP52.6, R51.1, U9.25
SCL9: JP57.6, JP58.6, R57.1, U10.25
SCL10: JP63.6, JP64.6, R63.1, U11.25
SCL11: JP69.6, JP70.6, R69.1, U12.25
SCL12: JP75.6, JP76.6, R75.1, U13.25
SCL13: JP81.6, JP82.6, R81.1, U14.25
SCL14: JP87.6, JP88.6, R87.1, U15.25
SCL15: JP93.6, JP94.6, R93.1, U16.25
SCL16: JP99.6, JP100.6, R99.1, U17.25
SCL17: JP105.6, JP106.6, R105.1, U18.25
SCL18: JP111.6, JP112.6, R111.1, U19.25
SCL19: JP117.6, JP118.6, R117.1, U20.25
SCL20: JP123.6, JP124.6, R123.1, U21.25
SCL21: JP129.6, JP130.6, R129.1, U22.25
SCL22: JP135.6, JP136.6, R135.1, U23.25
SCL23: JP141.6, JP142.6, R141.1, U24.25
SCL24: JP147.6, JP148.6, R147.1, U25.25
SCL25: JP153.6, JP154.6, R153.1, U26.25
SCL26: JP159.6, JP160.6, R159.1, U27.25
SCL27: JP165.6, JP166.6, R165.1, U28.25
SCL28: JP171.6, JP172.6, R171.1, U29.25
SCL29: JP177.6, JP178.6, R177.1, U30.25
SDA: JP1.5, JP2.5, R4.1, U1.24
SDA1: JP7.5, JP8.5, R8.1, U2.24
SDA2: JP15.5, JP16.5, R14.1, U3.24
SDA3: JP21.5, JP22.5, R20.1, U4.24
SDA4: JP27.5, JP28.5, R26.1, U5.24
SDA5: JP33.5, JP34.5, R32.1, U6.24
SDA6: JP39.5, JP40.5, R38.1, U7.24
SDA7: JP45.5, JP46.5, R44.1, U8.24
SDA8: JP51.5, JP52.5, R50.1, U9.24
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
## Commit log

2015-04-17 Adding .gitignore.
2015-04-17 Initial commit of v1.1
    - Added standoff holes
    - Changed I2C headers to match SparkFun standard
    - Added I2C pins to both sides to allow cascading boards.
    - Updated Eagle libraries
    - Updated 0402 packages to 0603.
    - Increase fiducial size
2015-04-17 Labeling SJ4 and SJ5.
2015-04-20 Adding silk around headers. Labeling SJ1.
2015-04-21 Revising GPIO headers to single 2x10 header.
2015-04-24 Reducing paste aperature on SX1509 pads. Removing extra bStops.
2015-04-24 Getting rid of one last bStop strip.
2015-04-24 Temporarily removing Arduino library (will subtree).
2015-04-24 Squashed 'Libraries/Arduino/' content from commit 08ad7b0
    git-subtree-dir: Libraries/Arduino
    git-subtree-split: 08ad7b0ec1d5bc0ac4824297f483f439bb08fdc4
2015-04-24 Adding README.MD to Libraries folder.
2015-05-14 Updating readmes
2015-05-14 Updating subtree directions
2015-05-29 Making power busses selectable. Moving silk.
    - Not defaulting the two power bus headers to either GND or VCC.
    - Adding two jumpers on each header to allow connecting them high or low.
    - This will make it easier to set up LEDs as either source or sink.
    - It'll also make it easier to short VCC to GND - will require extra
    caution using the jumpers.
2015-06-01 Defaulting power busses to GND. Moving SJ2&3.
2015-06-05 created panel v20
2015-09-23 Updating readme. Standardizing Production files directory name
2015-09-23 Squashed 'Libraries/Arduino/' content from commit 87ced48
    git-subtree-dir: Libraries/Arduino
    git-subtree-split: 87ced48f5688efb6576cbd1612476fe53a08c703
2015-09-23 Adding Arduino library as a subtree.
2015-09-23 Fixing hardware folder name
2015-09-23 Removing readme for old board
2015-09-23 Readme fixes
2015-09-24 Standardizing Eagle file names
2015-09-24 Removing old version of library.
2015-10-21 made panel v20 larger
2016-01-21 Updated Documentation
2016-01-21 Added product name to documentation
2022-01-27 Removing old library from repo. Point at current Arduino library repo.
